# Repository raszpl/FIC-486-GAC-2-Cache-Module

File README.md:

# FIC-486-GAC-2 Cache Module reproduction

Reverse Engineered non standard 256K L2 Cache Module for use in:

- AT&T GLOBALYST 510 = NCR 3228 = [FIC 486-GAC-2](https://theretroweb.com/motherboards/s/fic-486-gac-2)
- AT&T GLOBALYST 515 = NCR 3232 = [FIC 486-GAC-2](https://theretroweb.com/motherboards/s/fic-486-gac-2)

Potentially also:
- AT&T Globalyst 520 = NCR 3238 = [FIC 486-PAK-3](https://theretroweb.com/motherboards/s/fic-486-pak-3)/[Vogons: What´s wrong with this FIC 486 PAK-3 ??](https://www.vogons.org/viewtopic.php?t=80951) needs confirmation
- AT&T Globalyst 530 = NCR 3338 = [FIC 486-PAK-3](https://theretroweb.com/motherboards/s/fic-486-pak-3) needs confirmation
- NCR 3231
- AT&T Globalyst 525 = NCR 3253

**Incompatible** platforms also reusing VLB slot for Cache:
- AT&T
  - pre 1993 Globalyst name change [NCR MODEL 3230 (A4923 ISA)](https://theretroweb.com/motherboards/s/ncr-model-3230-a4923-isa) Uses VLB slot form factor, but in an edge connector form [Vogons: NCR 3230-7020 486 DX 33 System - Cache question?](https://www.vogons.org/viewtopic.php?p=1447953#p1447953)
  - [Globalyst 550 = NCR 3246](https://theretroweb.com/motherboards/s/at-t-globalyst-550-class-3246) 
  - Globalyst 575 = NCR 3347 both use [517-0002811](https://raw.githubusercontent.com/raszpl/FIC-486-GAC-2-Cache-Module/refs/heads/main/not%20compatible%20proprietary%20vlb%20cache%20modules/ATT-Globalyst_550_575.jpg)
- Compaq
  - [ProLinea 4/66 (164560-001)](https://theretroweb.com/motherboards/s/compaq-prolinea-4-66)
  - [ProLinea MT/833CDS/850/850CDS/860CDS/866 (197023-001)](https://theretroweb.com/motherboards/s/compaq-prolinea-mt)
  - [Presario 700-900 series (171009-001)](https://theretroweb.com/motherboards/s/compaq-presario-700-900-series-486) all three use 128KB 197005-001 (003670-001) [front](https://raw.githubusercontent.com/raszpl/FIC-486-GAC-2-Cache-Module/refs/heads/main/not%20compatible%20proprietary%20vlb%20cache%20modules/Compaq%20197005-001.jpg) [back](https://raw.githubusercontent.com/raszpl/FIC-486-GAC-2-Cache-Module/refs/heads/main/not%20compatible%20proprietary%20vlb%20cache%20modules/Compaq%20197005-001%20back.jpg) [in slot](https://raw.githubusercontent.com/raszpl/FIC-486-GAC-2-Cache-Module/refs/heads/main/not%20compatible%20proprietary%20vlb%20cache%20modules/Compaq%20197005-001%20in%20slot.jpg) or 128KB 197050-001 (003454-001) [front](https://raw.githubusercontent.com/raszpl/FIC-486-GAC-2-Cache-Module/refs/heads/main/not%20compatible%20proprietary%20vlb%20cache%20modules/Compaq%20197050-001.jpg) [back](https://raw.githubusercontent.com/raszpl/FIC-486-GAC-2-Cache-Module/refs/heads/main/not%20compatible%20proprietary%20vlb%20cache%20modules/Compaq%20197050-001%20back.jpg). 100% working DIY **[256KB/1MB Replacement](https://github.com/wichers/Compaq-Cache-Module-197005-001)** by [sander wichers](https://www.vogons.org/viewtopic.php?t=102242) inspired by this project :)
  - [Prosignia VS](https://www.digitaldungeon.be/digitaldungeon/computer/compaq/prosignia-vs_01/prosignia-vs_01.html) uses Sony CXK784862Q-33 based 256KB 194380-001 [front](/not%20compatible%20proprietary%20vlb%20cache%20modules/Compaq%20194380-001.jpg?raw=true) [back](https://raw.githubusercontent.com/raszpl/FIC-486-GAC-2-Cache-Module/refs/heads/main/not%20compatible%20proprietary%20vlb%20cache%20modules/Compaq%20194380-001%20back.jpg)
  - [DESKPRO XE 486](https://theretroweb.com/motherboards/s/compaq-deskpro-xe-486) uses Sony CXK784862Q-33 based 256KB Kingston KTC-4358 [front](https://raw.githubusercontent.com/raszpl/FIC-486-GAC-2-Cache-Module/refs/heads/main/not%20compatible%20proprietary%20vlb%20cache%20modules/Kingston%20KTC-4358.jpg) [in slot](https://raw.githubusercontent.com/raszpl/FIC-486-GAC-2-Cache-Module/refs/heads/main/not%20compatible%20proprietary%20vlb%20cache%20modules/Kingston%20KTC-4358%20inside%20deskpro-xe-486.jpg). Maybe 194380-001 compatible?
  - [Deskpro/i Family 3](https://theretroweb.com/motherboards/s/compaq-deskpro-i-family-3-25i-rev-1-p-n-002) uses Intel A82485-33 based 64KB 141345-001 (002581)
  - [Deskpro/i Family 4](https://theretroweb.com/motherboards/s/compaq-deskpro-i-family-4-25is-rev-3-p-n-00) uses Intel A82485-33 based 64KB 141477-001 (002754) [front](https://raw.githubusercontent.com/raszpl/FIC-486-GAC-2-Cache-Module/refs/heads/main/not%20compatible%20proprietary%20vlb%20cache%20modules/Compaq%20002754-001.jpg) [back](https://raw.githubusercontent.com/raszpl/FIC-486-GAC-2-Cache-Module/refs/heads/main/not%20compatible%20proprietary%20vlb%20cache%20modules/Compaq%20002754-001%20back.jpg)
- [HP Vectra VE 4](https://theretroweb.com/motherboards/s/hp-vectra-ve-4-xxx-d3501) uses 256KB HP D2465A/IDT 7MP6193 [front](https://raw.githubusercontent.com/raszpl/FIC-486-GAC-2-Cache-Module/refs/heads/main/not%20compatible%20proprietary%20vlb%20cache%20modules/HP%20Vectra%20VE%204%20256%20KB%20Cache%20D2465A.webp) [back](https://raw.githubusercontent.com/raszpl/FIC-486-GAC-2-Cache-Module/refs/heads/main/not%20compatible%20proprietary%20vlb%20cache%20modules/HP%20Vectra%20VE%204%20256%20KB%20Cache%20D2465A%20back.webp)
- [HPE NetServer LC 5/166 (D4861AR)](https://theretroweb.com/motherboards/s/hp-netserver-lc) uses 256KB HP D3322A/IDT 7MP6152 (HP 0960-0899) [front](https://raw.githubusercontent.com/raszpl/FIC-486-GAC-2-Cache-Module/refs/heads/main/not%20compatible%20proprietary%20vlb%20cache%20modules/7MP6152.jpg)
- [Olivetti M4 454 S](https://theretroweb.com/motherboards/s/olivetti-m4-4x4) uses 128KB CYM9236 and 256KB CYM9237PB [front](https://raw.githubusercontent.com/raszpl/FIC-486-GAC-2-Cache-Module/refs/heads/main/not%20compatible%20proprietary%20vlb%20cache%20modules/CYM9236.jpg) [back](https://raw.githubusercontent.com/raszpl/FIC-486-GAC-2-Cache-Module/refs/heads/main/not%20compatible%20proprietary%20vlb%20cache%20modules/CYM9236%20back.jpg) [with slot](https://raw.githubusercontent.com/raszpl/FIC-486-GAC-2-Cache-Module/refs/heads/main/not%20compatible%20proprietary%20vlb%20cache%20modules/CYM9236%20and%20slot.jpg)
- [Siemens Nixdorf FD200 D882](https://theretroweb.com/motherboards/s/siemens-nixdorf-system-board-d882) uses 256KB CYM9252PB [front](https://raw.githubusercontent.com/raszpl/FIC-486-GAC-2-Cache-Module/refs/heads/main/not%20compatible%20proprietary%20vlb%20cache%20modules/Siemens%20Nixdorf%20FD200%20D882%20cym9252pb.JPG) [back](https://raw.githubusercontent.com/raszpl/FIC-486-GAC-2-Cache-Module/refs/heads/main/not%20compatible%20proprietary%20vlb%20cache%20modules/Siemens%20Nixdorf%20FD200%20D882%20cym9252pb%20back.JPG) and unknown 128KB one.
## Resources
Pictures of the original "DOC: 13630" "ASSY: 008-0078204 A" Cache module:

rev 2 [front ](https://raw.githubusercontent.com/raszpl/FIC-486-GAC-2-Cache-Module/main/img/DOC13630.jpg)

rev 2.1 [front ](https://raw.githubusercontent.com/raszpl/FIC-486-GAC-2-Cache-Module/main/img/P1220276.JPG), [back ](https://raw.githubusercontent.com/raszpl/FIC-486-GAC-2-Cache-Module/main/img/P1220275.JPG)

[plugged into FIC 486-GAC-2](https://raw.githubusercontent.com/raszpl/FIC-486-GAC-2-Cache-Module/main/img/P1220281.JPG)

-----
[Vogons: FIC 486-GAC-2 proprietary cache module - open source reproduction *Completed*](https://www.vogons.org/viewtopic.php?f=46&t=94550) thread:
>majestyk: "FIC sold two different versions with different pinouts (and the same "VLB"-socket). Only the one in the pictures works on a 486-GAC2 and a few other FIC mainboards."

This project was only possible with help provided by majestyk - owner of this very rare Cache module, and RockstarRunner - FIC 486-GAC-2 owner looking for said Cache module. Huge thanks for taking time to capture high resolution pictures and validating progress with measurements.

[UMC UM61256A 32K x 8 Static RAM datasheet](/doc/UMC_UM61256A.pdf)

[VESA VLB slot pinout](/doc/VLB_pins.png) [VESA VLB slot dimensions](/doc/vlb-edge-conn.png)

## Status

100%. Manufactured and tested. Preliminary design took 8 days. Fixes after assembling first prototype 2 days.

## Progress report
4/19/2024: Rev 2.4 assembled by swapping components from Rev 2.2. CACHECHK screenshot.

4/15/2024: Rev 2.4 'Pcbs turned up! We have edge connectors this time 😆'

3/23/2024: [Final Rev 2.4](https://raw.githubusercontent.com/raszpl/FIC-486-GAC-2-Cache-Module/main/img/FIC%20486-GAC-2%20cache%20Final%20rev2.4.png). Reworked SRAM footprint for easier hand soldering, slightly optimized capacitor placement.

2/29/2024: [Final Rev 2.3](https://raw.githubusercontent.com/raszpl/FIC-486-GAC-2-Cache-Module/main/img/FIC%20486-GAC-2%20cache%20Final%20rev2.3.png). Slightly thicker tracks and silkscreen text, additional clearance work. Shrank from initial prototype, should be almost equal height of original. Height when inserted 26.3mm, height including slot 33.6mm. 

2/28/2024: Prototypes assembled after sanding off soldermask from edge slot contacts, didnt work at first try. Turns out I swapped few power/ground pins in the connector resulting in dead short. Great sleuthing by Miisalo uncovered this mishap, after cutting bad connections we have sucessfull boot.

2/27/2024: Prototypes arrived. Who can spot the problem?

Will require some finessing with sandpaper to uncover edge slot pads :)

2/11/2024: [99% done](https://raw.githubusercontent.com/raszpl/FIC-486-GAC-2-Cache-Module/main/img/FIC%20486-GAC-2%20cache%20coast%20VIP%2099%25.png), ERC&DRC 0 errors 0 warnings. Footprints should be correct now. Gerbers sent for manufacturing.

2/8/2024: [95% there](https://raw.githubusercontent.com/raszpl/FIC-486-GAC-2-Cache-Module/main/img/FIC%20486-GAC-2%20cache%20coast%20VIP%2095%25.png), 0 errors, 7 Warnings. 5 connections missing, 11 guesses and assumptions on U1 U2 and some more on common lines.

2/6/2024: [90% there](https://raw.githubusercontent.com/raszpl/FIC-486-GAC-2-Cache-Module/main/img/FIC%20486-GAC-2%20cache%20coast%20VIP%2090%25.png), 0 errors 18 warnings. Just a couple tracks left.

2/5/2024: [80% there](https://raw.githubusercontent.com/raszpl/FIC-486-GAC-2-Cache-Module/main/img/FIC%20486-GAC-2%20cache%20coast%20VIP%2080%25.png), 0 drc errors, 62 violations. Still bad footprints and I havent gotten around to fixing power/ground pins. Whats left is figuring LS244 address buffering mapping, TAG ram address and output pins to edge mapping, WE/CE/OE mapping to edge.

2/4/2024: Very VIP, only about 50% there at the moment.

02/3/2024: Project start. Figuring out how to make edge connector footprint, searching for SOJ-28L footprint.

-----------------
# Work for hire
Interested in having a piece of hardware reverse engineered/cloned? Drop me an [email](https://github.com/raszpl).

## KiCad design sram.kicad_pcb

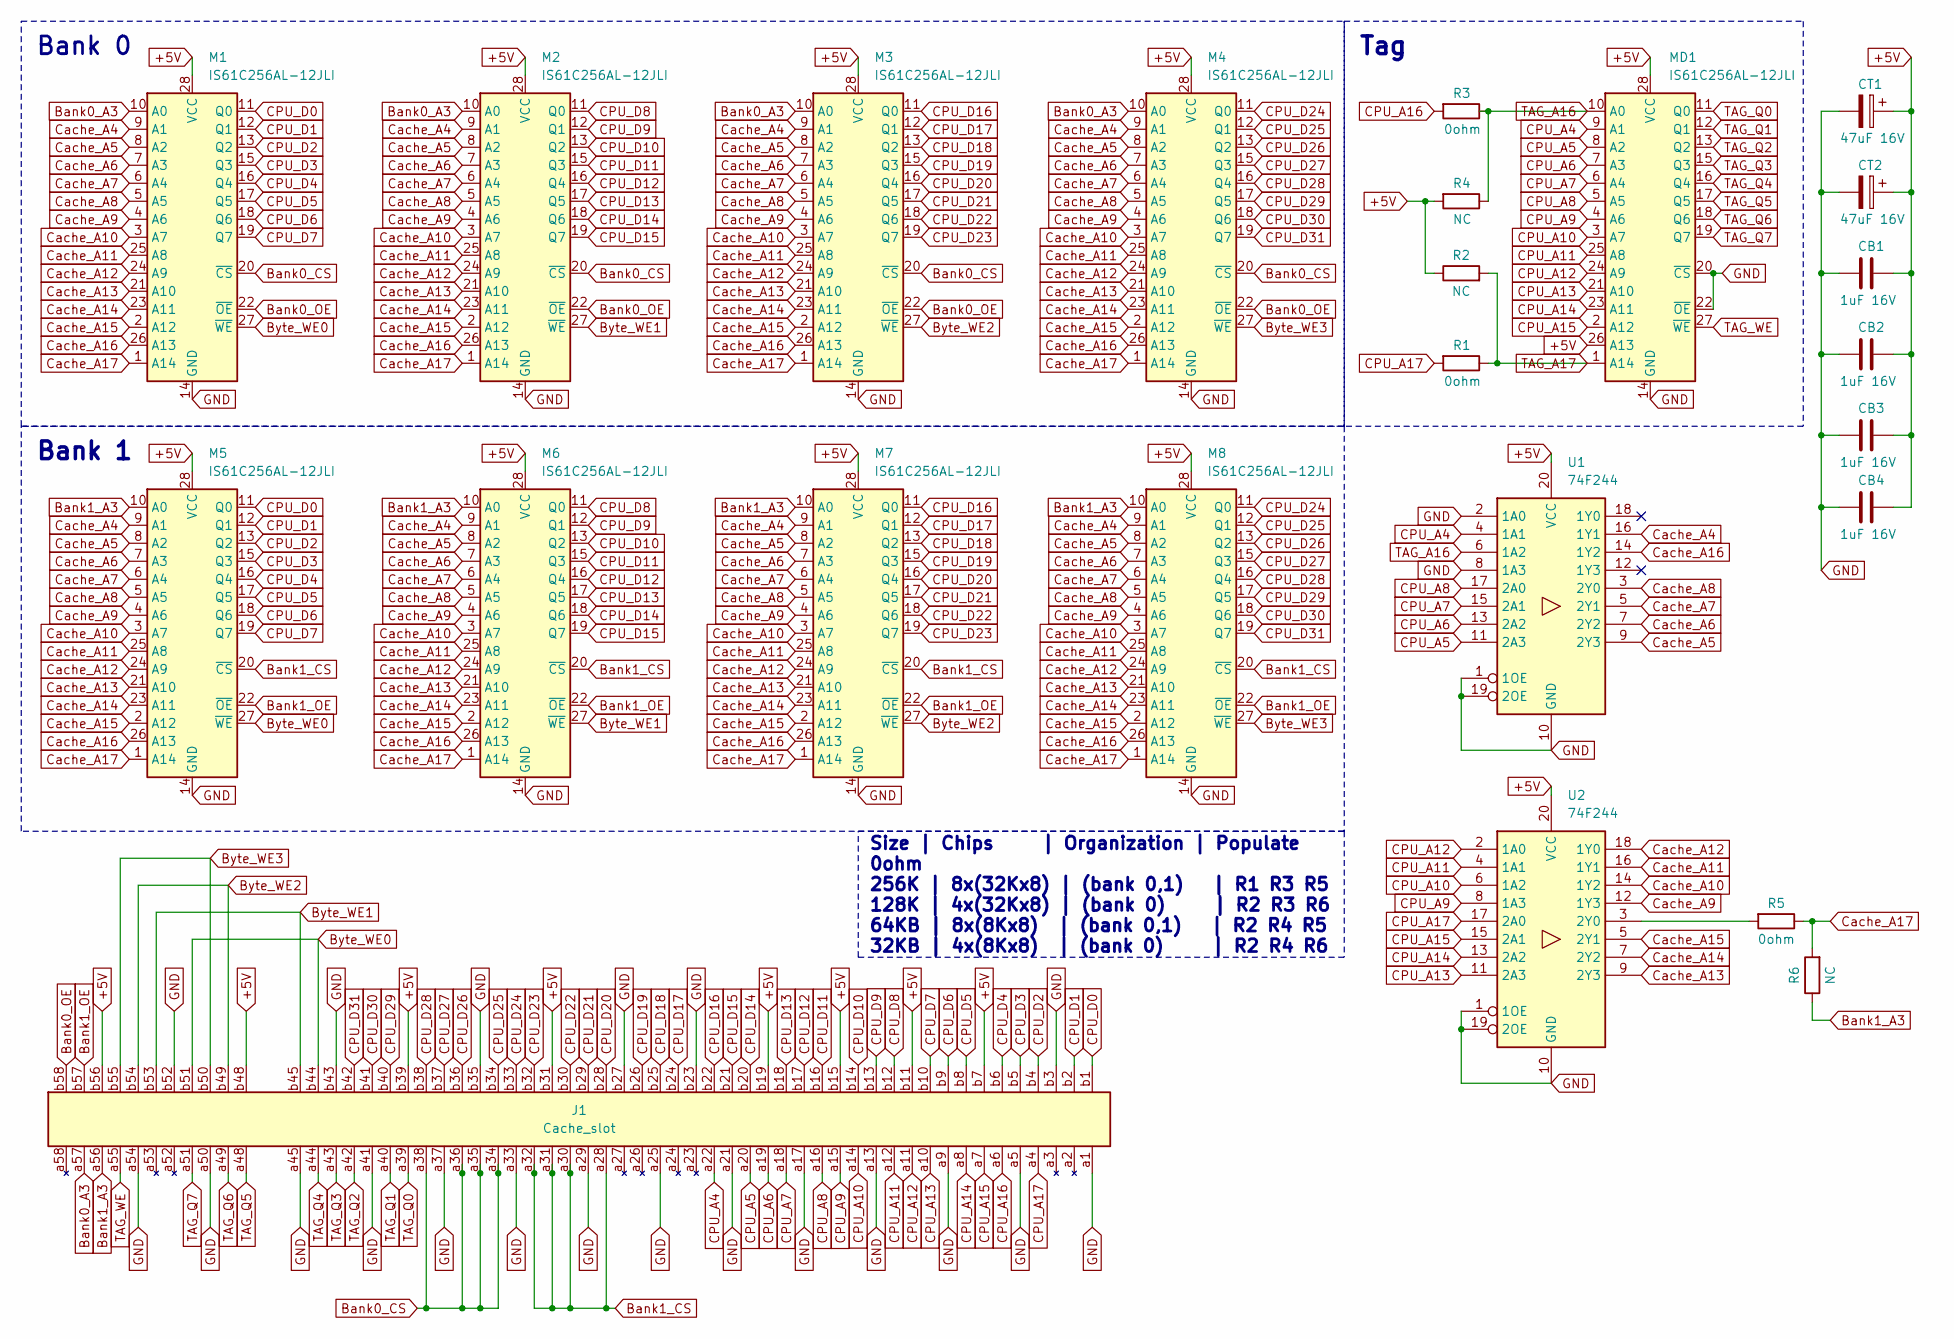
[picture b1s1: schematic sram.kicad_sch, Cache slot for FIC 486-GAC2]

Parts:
CB1, CB2, CB3, CB4: 1uF 16V; C_0805_2012Metric
CT1, CT2: 47uF 16V; C_1206_3216Metric_Pad1.33x1.80mm_HandSolder
J1: Cache_slot; Cache slot
M1, M2, M3, M4, M5, M6, M7, M8: IS61C256AL-12JLI; SOIC-28 very wide
MD1: IS61C256AL-12JLI; SOIC-28 very wide
R1, R3, R5: 0ohm; R_0805_2012Metric
R2, R4, R6: NC; R_0805_2012Metric
U1, U2: 74F244; SOIC-20W_7.5x12.8mm_P1.27mm

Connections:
+5V: CB1.1, CB2.1, CB3.1, CB4.1, CT1.1, CT2.1, J1.b7, J1.b11, J1.b15, J1.b19, J1.b31, J1.b39, J1.b48, J1.b56, M1.28 (VCC), M2.28 (VCC), M3.28 (VCC), M4.28 (VCC), M5.28 (VCC), M6.28 (VCC), M7.28 (VCC), M8.28 (VCC), MD1.26 (A13), MD1.28 (VCC), R2.1, R4.2, U1.20 (VCC), U2.20 (VCC)
Bank0_A3: J1.a57, M1.10 (A0), M2.10 (A0), M3.10 (A0), M4.10 (A0)
Bank0_CS: J1.a34, J1.a35, J1.a36, J1.a38, M1.20 (~CS), M2.20 (~CS), M3.20 (~CS), M4.20 (~CS)
Bank0_OE: J1.b58, M1.22 (~OE), M2.22 (~OE), M3.22 (~OE), M4.22 (~OE)
Bank1_A3: J1.a56, M5.10 (A0), M6.10 (A0), M7.10 (A0), M8.10 (A0), R6.1
Bank1_CS: J1.a28, J1.a30, J1.a31, J1.a32, M5.20 (~CS), M6.20 (~CS), M7.20 (~CS), M8.20 (~CS)
Bank1_OE: J1.b57, M5.22 (~OE), M6.22 (~OE), M7.22 (~OE), M8.22 (~OE)
Byte_WE0: J1.b44, J1.b51, M1.27 (~WE), M5.27 (~WE)
Byte_WE1: J1.b45, J1.b53, M2.27 (~WE), M6.27 (~WE)
Byte_WE2: J1.b49, J1.b54, M3.27 (~WE), M7.27 (~WE)
Byte_WE3: J1.b50, J1.b55, M4.27 (~WE), M8.27 (~WE)
CPU_A4: J1.a22, MD1.9 (A1), U1.4 (1A1)
CPU_A5: J1.a20, MD1.8 (A2), U1.11 (2A3)
CPU_A6: J1.a19, MD1.7 (A3), U1.13 (2A2)
CPU_A7: J1.a18, MD1.6 (A4), U1.15 (2A1)
CPU_A8: J1.a16, MD1.5 (A5), U1.17 (2A0)
CPU_A9: J1.a15, MD1.4 (A6), U2.8 (1A3)
CPU_A10: J1.a14, MD1.3 (A7), U2.6 (1A2)
CPU_A11: J1.a12, MD1.25 (A8), U2.4 (1A1)
CPU_A12: J1.a11, MD1.24 (A9), U2.2 (1A0)
CPU_A13: J1.a10, MD1.21 (A10), U2.11 (2A3)
CPU_A14: J1.a8, MD1.23 (A11), U2.13 (2A2)
CPU_A15: J1.a7, MD1.2 (A12), U2.15 (2A1)
CPU_A16: J1.a6, R3.2
CPU_A17: J1.a4, R1.2, U2.17 (2A0)
CPU_D0: J1.b1, M1.11 (Q0), M5.11 (Q0)
CPU_D1: J1.b2, M1.12 (Q1), M5.12 (Q1)
CPU_D2: J1.b4, M1.13 (Q2), M5.13 (Q2)
CPU_D3: J1.b5, M1.15 (Q3), M5.15 (Q3)
CPU_D4: J1.b6, M1.16 (Q4), M5.16 (Q4)
CPU_D5: J1.b8, M1.17 (Q5), M5.17 (Q5)
CPU_D6: J1.b9, M1.18 (Q6), M5.18 (Q6)
CPU_D7: J1.b10, M1.19 (Q7), M5.19 (Q7)
CPU_D8: J1.b12, M2.11 (Q0), M6.11 (Q0)
CPU_D9: J1.b13, M2.12 (Q1), M6.12 (Q1)
CPU_D10: J1.b14, M2.13 (Q2), M6.13 (Q2)
CPU_D11: J1.b16, M2.15 (Q3), M6.15 (Q3)
CPU_D12: J1.b17, M2.16 (Q4), M6.16 (Q4)
CPU_D13: J1.b18, M2.17 (Q5), M6.17 (Q5)
CPU_D14: J1.b20, M2.18 (Q6), M6.18 (Q6)
CPU_D15: J1.b21, M2.19 (Q7), M6.19 (Q7)
CPU_D16: J1.b22, M3.11 (Q0), M7.11 (Q0)
CPU_D17: J1.b24, M3.12 (Q1), M7.12 (Q1)
CPU_D18: J1.b25, M3.13 (Q2), M7.13 (Q2)
CPU_D19: J1.b26, M3.15 (Q3), M7.15 (Q3)
CPU_D20: J1.b28, M3.16 (Q4), M7.16 (Q4)
CPU_D21: J1.b29, M3.17 (Q5), M7.17 (Q5)
CPU_D22: J1.b30, M3.18 (Q6), M7.18 (Q6)
CPU_D23: J1.b32, M3.19 (Q7), M7.19 (Q7)
CPU_D24: J1.b33, M4.11 (Q0), M8.11 (Q0)
CPU_D25: J1.b34, M4.12 (Q1), M8.12 (Q1)
CPU_D26: J1.b36, M4.13 (Q2), M8.13 (Q2)
CPU_D27: J1.b37, M4.15 (Q3), M8.15 (Q3)
CPU_D28: J1.b38, M4.16 (Q4), M8.16 (Q4)
CPU_D29: J1.b40, M4.17 (Q5), M8.17 (Q5)
CPU_D30: J1.b41, M4.18 (Q6), M8.18 (Q6)
CPU_D31: J1.b42, M4.19 (Q7), M8.19 (Q7)
Cache_A4: M1.9 (A1), M2.9 (A1), M3.9 (A1), M4.9 (A1), M5.9 (A1), M6.9 (A1), M7.9 (A1), M8.9 (A1), U1.16 (1Y1)
Cache_A5: M1.8 (A2), M2.8 (A2), M3.8 (A2), M4.8 (A2), M5.8 (A2), M6.8 (A2), M7.8 (A2), M8.8 (A2), U1.9 (2Y3)
Cache_A6: M1.7 (A3), M2.7 (A3), M3.7 (A3), M4.7 (A3), M5.7 (A3), M6.7 (A3), M7.7 (A3), M8.7 (A3), U1.7 (2Y2)
Cache_A7: M1.6 (A4), M2.6 (A4), M3.6 (A4), M4.6 (A4), M5.6 (A4), M6.6 (A4), M7.6 (A4), M8.6 (A4), U1.5 (2Y1)
Cache_A8: M1.5 (A5), M2.5 (A5), M3.5 (A5), M4.5 (A5), M5.5 (A5), M6.5 (A5), M7.5 (A5), M8.5 (A5), U1.3 (2Y0)
Cache_A9: M1.4 (A6), M2.4 (A6), M3.4 (A6), M4.4 (A6), M5.4 (A6), M6.4 (A6), M7.4 (A6), M8.4 (A6), U2.12 (1Y3)
Cache_A10: M1.3 (A7), M2.3 (A7), M3.3 (A7), M4.3 (A7), M5.3 (A7), M6.3 (A7), M7.3 (A7), M8.3 (A7), U2.14 (1Y2)
Cache_A11: M1.25 (A8), M2.25 (A8), M3.25 (A8), M4.25 (A8), M5.25 (A8), M6.25 (A8), M7.25 (A8), M8.25 (A8), U2.16 (1Y1)
Cache_A12: M1.24 (A9), M2.24 (A9), M3.24 (A9), M4.24 (A9), M5.24 (A9), M6.24 (A9), M7.24 (A9), M8.24 (A9), U2.18 (1Y0)
Cache_A13: M1.21 (A10), M2.21 (A10), M3.21 (A10), M4.21 (A10), M5.21 (A10), M6.21 (A10), M7.21 (A10), M8.21 (A10), U2.9 (2Y3)
Cache_A14: M1.23 (A11), M2.23 (A11), M3.23 (A11), M4.23 (A11), M5.23 (A11), M6.23 (A11), M7.23 (A11), M8.23 (A11), U2.7 (2Y2)
Cache_A15: M1.2 (A12), M2.2 (A12), M3.2 (A12), M4.2 (A12), M5.2 (A12), M6.2 (A12), M7.2 (A12), M8.2 (A12), U2.5 (2Y1)
Cache_A16: M1.26 (A13), M2.26 (A13), M3.26 (A13), M4.26 (A13), M5.26 (A13), M6.26 (A13), M7.26 (A13), M8.26 (A13), U1.14 (1Y2)
Cache_A17: M1.1 (A14), M2.1 (A14), M3.1 (A14), M4.1 (A14), M5.1 (A14), M6.1 (A14), M7.1 (A14), M8.1 (A14), R5.1, R6.2
GND: CB1.2, CB2.2, CB3.2, CB4.2, CT1.2, CT2.2, J1.a1, J1.a5, J1.a9, J1.a13, J1.a17, J1.a21, J1.a25, J1.a29, J1.a33, J1.a37, J1.a41, J1.a45, J1.a50, J1.a54, J1.b3, J1.b23, J1.b27, J1.b35, J1.b43, J1.b52, M1.14 (GND), M2.14 (GND), M3.14 (GND), M4.14 (GND), M5.14 (GND), M6.14 (GND), M7.14 (GND), M8.14 (GND), MD1.14 (GND), MD1.20 (~CS), MD1.22 (~OE), U1.1 (1OE), U1.2 (1A0), U1.8 (1A3), U1.10 (GND), U1.19 (2OE), U2.1 (1OE), U2.10 (GND), U2.19 (2OE)
unnamed: R5.2, U2.3 (2Y0)
TAG_A16: MD1.10 (A0), R3.1, R4.1, U1.6 (1A2)
TAG_A17: MD1.1 (A14), R1.1, R2.2
TAG_Q0: J1.a39, MD1.11 (Q0)
TAG_Q1: J1.a40, MD1.12 (Q1)
TAG_Q2: J1.a42, MD1.13 (Q2)
TAG_Q3: J1.a43, MD1.15 (Q3)
TAG_Q4: J1.a44, MD1.16 (Q4)
TAG_Q5: J1.a48, MD1.17 (Q5)
TAG_Q6: J1.a49, MD1.18 (Q6)
TAG_Q7: J1.a51, MD1.19 (Q7)
TAG_WE: J1.a55, MD1.27 (~WE)

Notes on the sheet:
Bank 0
Tag
Size | Chips | Organization | Populate 0ohm 256K | 8x(32Kx8) | (bank 0,1) | R1 R3 R5 128K | 4x(32Kx8) | (bank 0) | R2 R3 R6 64KB | 8x(8Kx8) | (bank 0,1) | R2 R4 R5 32KB | 4x(8Kx8) | (bank 0) | R2 R4 R6
Bank 1

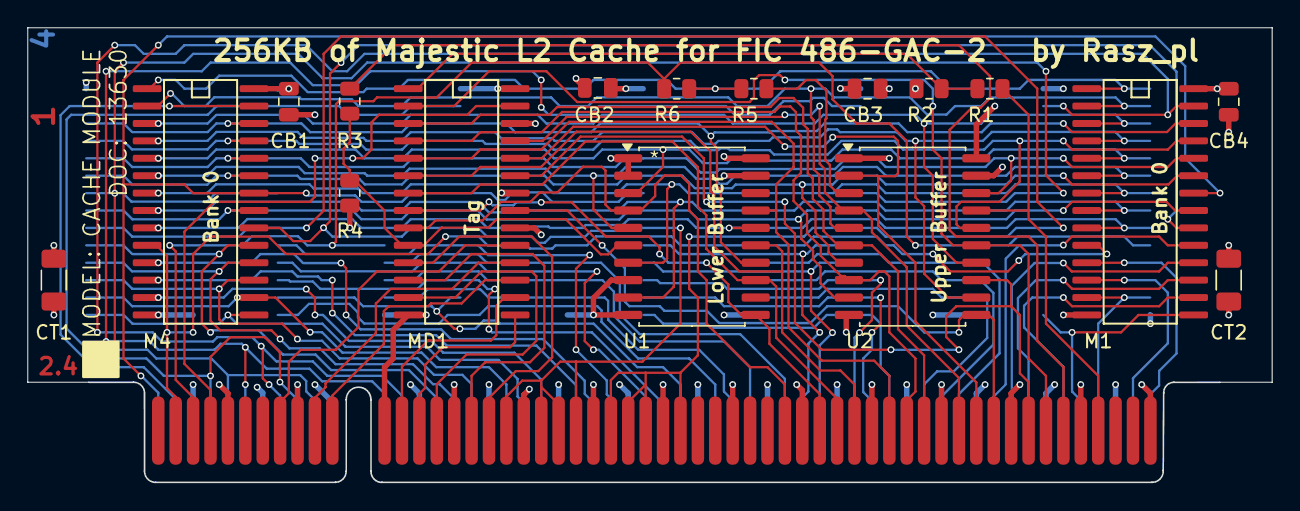
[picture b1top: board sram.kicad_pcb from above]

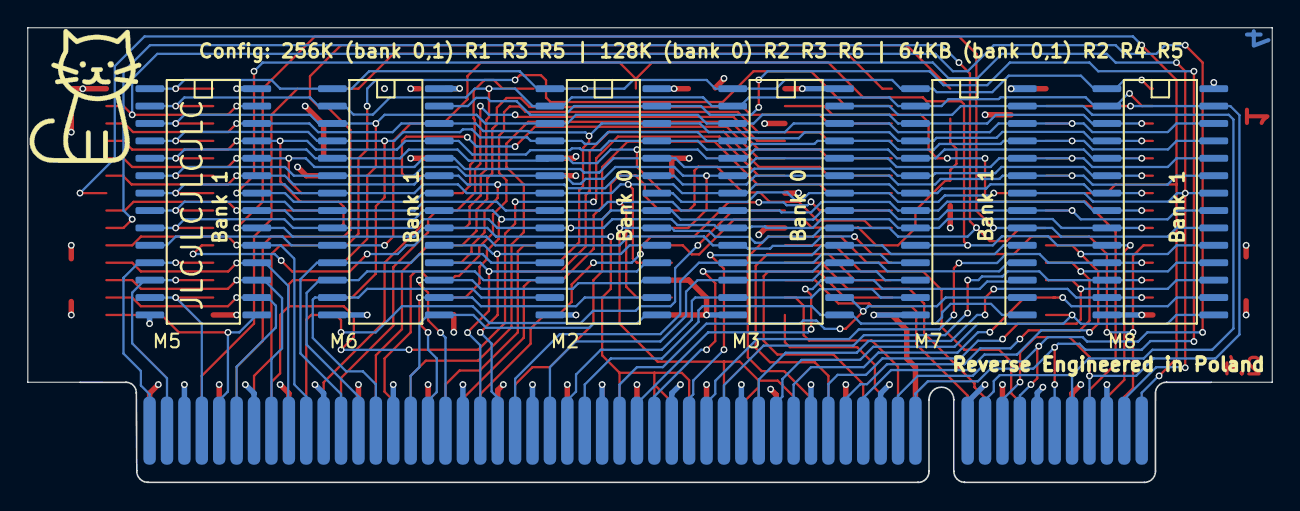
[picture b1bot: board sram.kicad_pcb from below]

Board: 4 copper layers, 90.7 x 33.1 mm, 24 parts (6 on the bottom side), 84 nets.

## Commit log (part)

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2024-02-05 Update README.md
    first version
2024-02-05 First day of work
2024-02-05 miniatures
2024-02-05 README.md fixed miniatures
2024-02-05 3 errors, 76 warnings
2024-02-06 0 drc errors, 62 violations
2024-02-06 steady progress
2024-02-06 90% progress update
2024-02-06 90% there, 0 errors 18 warnings. Just a couple tracks left.
2024-02-08 progress reports
2024-02-08 95% there
2024-02-08 95% there, 0 errors, 7 Warnings. 5 connections missing, 11 guesses and assumptions on U1 U2 and some more on common lines.
2024-02-10 99% done, ERC DRC 0 errors 0 warnings
2024-02-10 dummy to create folder
2024-02-11 are we done?
2024-02-11 result
2024-02-11 done?
2024-02-11 image links rebased
2024-02-11 config description correction
2024-02-11 gerbers
2024-02-13 new directory
2024-02-13 directory created
2024-02-13 original module rev 2
2024-02-29 Final Rev 2.3
2024-02-29 Final rev2.3 diagram
2024-03-23 Final version 2.4
2024-03-23 Update README.md date
2024-08-23 Compaq 197005-001
2024-08-23 Compaq 194380-001
2024-08-23 Update README.md added more incompatible Compaq examples
2024-08-23 CYM9236 7MP6152
2024-08-23 Update README.md Olivetti M4 454 S
2024-08-23 Update README.md HPE NetServer LC 5/166 (D4861AR)
2024-08-23 Compaq 002754-001
2024-08-23 Rename 002754-001.jpg to Compaq 002754-001.jpg
2024-08-23 Rename 002754-001 back.jpg to Compaq 002754-001 back.jpg
2024-08-23 Update README.md added Deskpro
2024-08-29 Kingston KTC-4358
2024-10-08 Create 1
2024-10-08 Rename DOC13630.jpg to img/DOC13630.jpg
2024-10-08 Rename DOC13630c.jpg to img/DOC13630c.jpg
2024-10-08 Rename FIC 486-GAC-2 cache Final rev2.3.png to img/FIC 486-GAC-2 cache Final rev2.3.png
2024-10-08 Rename FIC 486-GAC-2 cache Final rev2.4.png to img/FIC 486-GAC-2 cache Final rev2.4.png
2024-10-08 Rename FIC 486-GAC-2 cache coast VIP 80%.png to img/FIC 486-GAC-2 cache coast VIP 80%.png
2024-10-08 Rename FIC 486-GAC-2 cache coast VIP 90%.png to img/FIC 486-GAC-2 cache coast VIP 90%.png
2024-10-08 Rename FIC 486-GAC-2 cache coast VIP 95%.png to img/FIC 486-GAC-2 cache coast VIP 95%.png
2024-10-08 Rename FIC 486-GAC-2 cache coast VIP 99%.png to img/FIC 486-GAC-2 cache coast VIP 99%.png
2024-10-08 Rename P1220275.JPG to img/P1220275.JPG
2024-10-08 Rename P1220275c.jpg to img/P1220275c.jpg
2024-10-08 Rename P1220276.JPG to img/P1220276.JPG
2024-10-08 Rename P1220276c.jpg to img/P1220276c.jpg
2024-10-08 Rename P1220281.JPG to img/P1220281.JPG
2024-10-08 Rename P1220281c.jpg to img/P1220281c.jpg
2024-10-08 Rename VLB_pins.png to img/VLB_pins.png
2024-10-08 Rename back render c.jpg to img/back render c.jpg
2024-10-08 Rename back render.png to img/back render.png
2024-10-08 Rename front render c.jpg to img/front render c.jpg
2024-10-08 Rename front render.png to img/front render.png
2024-10-08 Rename prototype in slot c.jpg to img/rev2.2 prototype in slot c.jpg
2024-10-08 Rename vlb-edge-conn.png to doc/vlb-edge-conn.png
2024-10-08 Rename VLB_pins.png to VLB_pins.png
2024-10-08 Rename UMC_UM61256A.pdf to doc/UMC_UM61256A.pdf
2024-10-08 Rename boot.jpg to img/boot.jpg
2024-10-08 Rename prototype in slot.jpg to img/rev2.2 prototype in slot.jpg
2024-10-08 Rename prototypes.jpg to img/rev2.2 prototypes.jpg
2024-10-08 Rename prototypes c.jpg to img/rev2.2 prototypes c.jpg
2024-10-08 Rename rev2.4 assembled prototype c.jpg to rev2.4 assembled c.jpg
2024-10-08 Rename rev2.4 assembled prototype.jpg to rev2.4 assembled.jpg
2024-10-08 Rename rev2.4 prototype in slot c.jpg to rev2.4 in slot c.jpg
2024-10-08 Rename rev2.4 prototype in slot.jpg to rev2.4 in slot.jpg
2024-10-08 Rename rev2.4 prototypes c.jpg to rev2.4 c.jpg
2024-10-08 Rename rev2.4 prototypes.jpg to rev2.4.jpg
2026-06-14 Update README.md image link fixes
2026-06-14 Update README.md image link fix
